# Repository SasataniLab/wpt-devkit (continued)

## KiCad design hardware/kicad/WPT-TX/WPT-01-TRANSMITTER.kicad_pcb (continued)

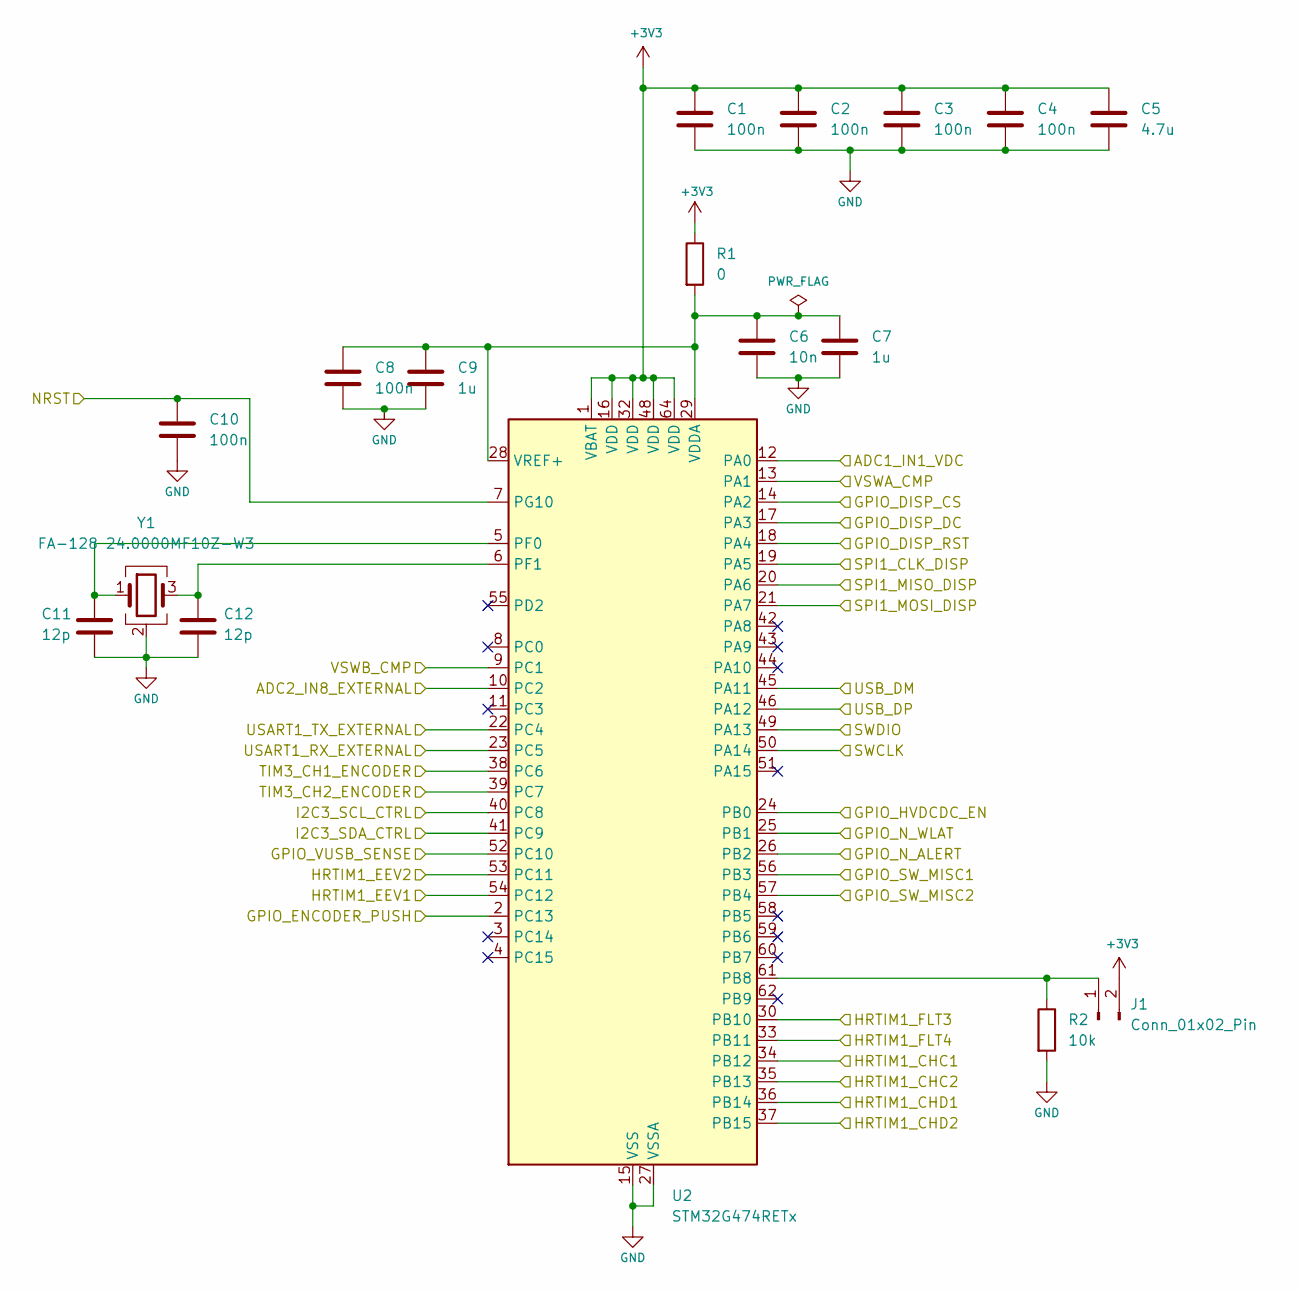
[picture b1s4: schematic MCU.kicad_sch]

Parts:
C1, C2, C3, C4, C8, C10: 100n; C_0402_1005Metric
C5: 4.7u; C_0402_1005Metric
C6: 10n; C_0402_1005Metric
C7, C9: 1u; C_0402_1005Metric
C11, C12: 12p; C_0402_1005Metric
J1: Conn_01x02_Pin; PinHeader_1x02_P2.54mm_Vertical
R1: 0; R_0402_1005Metric
R2: 10k; R_0402_1005Metric
U2: STM32G474RETx; LQFP-64_10x10mm_P0.5mm
Y1: FA-128 24.0000MF10Z-W3; Crystal_SMD_SeikoEpson_FA128-4Pin_2.0x1.6mm

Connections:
+3V3: C1.1, C2.1, C3.1, C4.1, C5.1, J1.2, R1.1, U2.1 (VBAT), U2.16 (VDD), U2.32 (VDD), U2.48 (VDD), U2.64 (VDD); also elsewhere on the board
/GPIO_VUSB_SENSE: U2.52 (PC10); also elsewhere on the board
/HRTIM1_CHC1: U2.34 (PB12); also elsewhere on the board
/HRTIM1_CHC2: U2.35 (PB13); also elsewhere on the board
/HRTIM1_CHD1: U2.36 (PB14); also elsewhere on the board
/HRTIM1_CHD2: U2.37 (PB15); also elsewhere on the board
/HRTIM1_EEV1: U2.54 (PC12); also elsewhere on the board
/HRTIM1_EEV2: U2.53 (PC11); also elsewhere on the board
/HRTIM1_FLT3: U2.30 (PB10); also elsewhere on the board
/HRTIM1_FLT4: U2.33 (PB11); also elsewhere on the board
/HV_EN_MCU: U2.24 (PB0); also elsewhere on the board
/HV_SW_STATE: U2.57 (PB4); also elsewhere on the board
/MCU/ADC2_IN8_EXTERNAL: U2.10 (PC2); also elsewhere on the board
/MCU/GPIO_DISP_CS: U2.14 (PA2); also elsewhere on the board
/MCU/GPIO_DISP_DC: U2.17 (PA3); also elsewhere on the board
/MCU/GPIO_DISP_RST: U2.18 (PA4); also elsewhere on the board
/MCU/GPIO_ENCODER_PUSH: U2.2 (PC13); also elsewhere on the board
/MCU/GPIO_SW_MISC1: U2.56 (PB3); also elsewhere on the board
/MCU/NRST: C10.1, U2.7 (PG10); also elsewhere on the board
/MCU/SPI1_CLK_DISP: U2.19 (PA5); also elsewhere on the board
/MCU/SPI1_MISO_DISP: U2.20 (PA6); also elsewhere on the board
/MCU/SPI1_MOSI_DISP: U2.21 (PA7); also elsewhere on the board
/MCU/SWCLK: U2.50 (PA14); also elsewhere on the board
/MCU/SWDIO: U2.49 (PA13); also elsewhere on the board
/MCU/TIM3_CH1_ENCODER: U2.38 (PC6); also elsewhere on the board
/MCU/TIM3_CH2_ENCODER: U2.39 (PC7); also elsewhere on the board
/MCU/USART1_RX_EXTERNAL: U2.23 (PC5); also elsewhere on the board
/MCU/USART1_TX_EXTERNAL: U2.22 (PC4); also elsewhere on the board
/USB_DM: U2.45 (PA11); also elsewhere on the board
/USB_DP: U2.46 (PA12); also elsewhere on the board
/VSWA_CMP: U2.13 (PA1); also elsewhere on the board
/VSWB_CMP: U2.9 (PC1); also elsewhere on the board
/WPT-01-TRANSMITTER-POWER/ADC_VDC: U2.12 (PA0); also elsewhere on the board
/WPT-01-TRANSMITTER-POWER/SCL: U2.40 (PC8); also elsewhere on the board
/WPT-01-TRANSMITTER-POWER/SDA: U2.41 (PC9); also elsewhere on the board
/WPT-01-TRANSMITTER-POWER/~ALERT: U2.26 (PB2); also elsewhere on the board
/WPT-01-TRANSMITTER-POWER/~WLAT: U2.25 (PB1); also elsewhere on the board
GND: C1.2, C2.2, C3.2, C4.2, C5.2, C6.2, C7.2, C8.2, C9.2, C10.2, C11.2, C12.2, R2.2, U2.15 (VSS), U2.27 (VSSA), U2.31 (VSS), U2.47 (VSS), U2.63 (VSS), Y1.2 (G), Y1.4 (G); also elsewhere on the board
unnamed: J1.1, R2.1, U2.61 (PB8)
unnamed: C11.1, U2.5 (PF0), Y1.1
unnamed: C12.1, U2.6 (PF1), Y1.3
unnamed: C6.1, C7.1, C8.1, C9.1, R1.2, U2.28 (VREF+), U2.29 (VDDA)

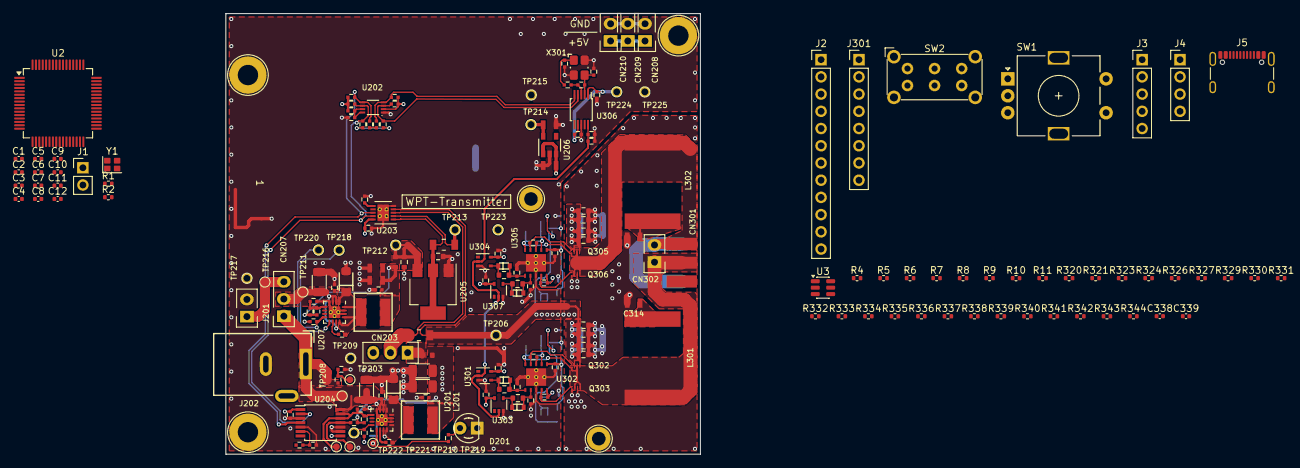
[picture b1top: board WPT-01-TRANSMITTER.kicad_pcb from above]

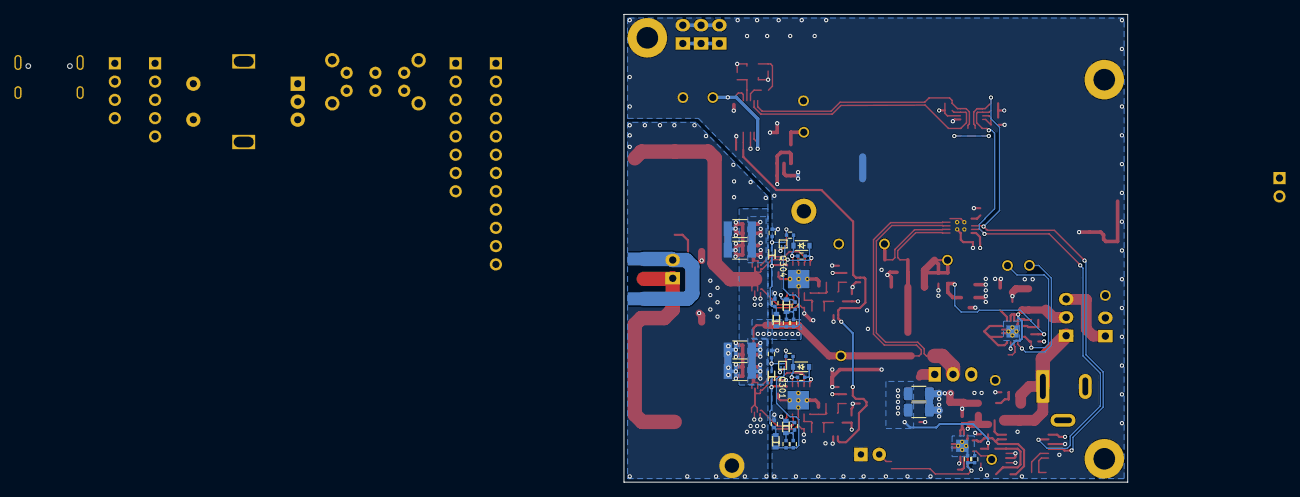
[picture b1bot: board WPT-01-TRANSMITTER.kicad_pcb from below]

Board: 4 copper layers, 70.0 x 65.0 mm, 230 parts (32 on the bottom side), 114 nets.

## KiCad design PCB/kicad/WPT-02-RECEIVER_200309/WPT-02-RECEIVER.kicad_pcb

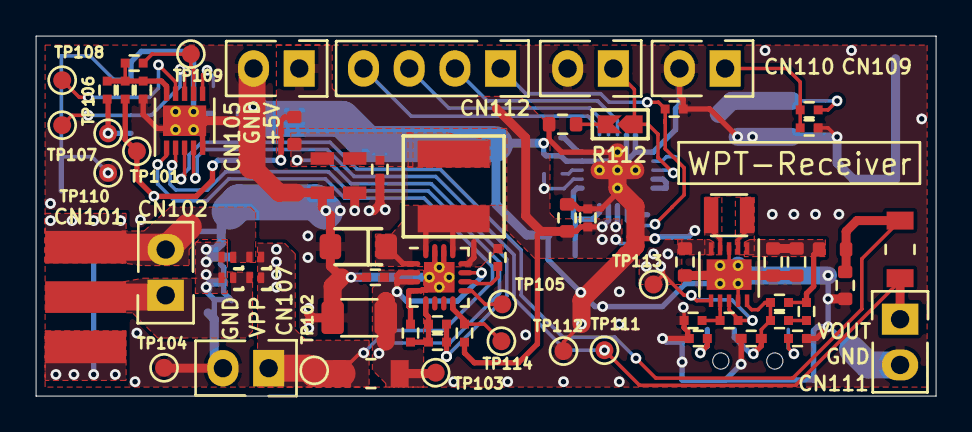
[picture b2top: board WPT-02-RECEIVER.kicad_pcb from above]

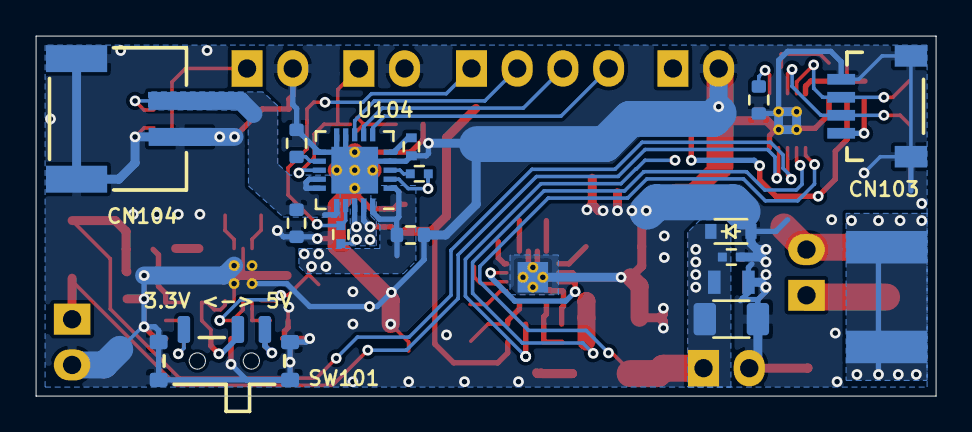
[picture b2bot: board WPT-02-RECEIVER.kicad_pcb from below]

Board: 4 copper layers, 50.0 x 20.0 mm, 84 parts (15 on the bottom side), 40 nets.

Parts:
C101: 0.022u/50(X7R); GRM15
C102, C107: 10u/50(X5R); GRM31
C103, C104, C116, C119: 0.1u/50(X7R); GRM15
C105: 1000p/50(C0G); GRM15
C106: 0.1u/100(X7R); GRM21
C108, C109: 22u/16(X5R); GRM21
C110: 10n/50(X7R); GRM15
C111: 10u/25(X5R); GRM18
C112, C122: 22u/10(X5R); GRM18
C113: 68p/50(C0G); GRM15
C117, C118, C120: 4.7u/16(X5R); GRM18
C123: OPEN; GRM18
CN101: CON-SMA-EDGE-S
CN102, CN105, CN107, CN109, CN110, CN111: ULO-PH409-1*2SF11; ULO-PH409-1x2SX1
CN103: SM04B-SRSS-TB(LF)(SN); SM04B-SRSS-TB
CN104: S2B-PH-SM4-TB(LF)(SN); S2B-PH-SM4-TB
CN112: ULO-PH409-1*4SF11; ULO-PH409-1x4SX1
D101, D102, D105, D106: PMEG6010AESBYL; SOD-993_Nexperia
D103: S210FA; SOD-123FA_OnSemi
D104: MM3Z39VT1G; SOD-323
FB101, FB102: BLM18PG330SN1D; BLM18
L101: NR5040T4R7N; NR5040
L102: DFE252012P-3R3M=P2; DFE252012C
R101: 82kF; R_0402
R102: 18kF; R_0402
R103, R107: 27mF(1/4W); R_1206
R104, R116: 10kF; R_0402
R105, R106, R108, R114, R119: OPEN; R_0402
R109: 750kF; R_0402
R110: 91kF; R_0402
R111: 820kF; R_0402
R112: SHORT_JUMPER; JP_SMD
R113, R115: 0; R_0402
R117: 0; R_0603
R118: NCP15XH103F03RC; NTC_0402
R120, R126: 100kF; R_0402
R121: 143kF; R_0402
R123: 100kF; R_0603
R124: 10kF; R_0603
SW101: CUS-12TB
TP101, TP102, TP103, TP104, TP105, TP106, TP107, TP108, TP109, TP110, TP111, TP112, TP113, TP114: TP1.0; TP_1mm
U101: TS30042-M000QFNR; QFN-16-1EP_3x3mm_Pitch0.5mm_Semtech
U102: MP2155GQ-Z; DFN-10-1EP_3x3mm_Pitch0.5mm_MPS
U103: PAC1720-1-AIA-TR; DFN-10-1EP_3x3mm_Pitch0.5mm_microchip_9Q
U104: MCP73871T-1CCI_ML; QFN-20-1EP_4x4mm_Pitch0.5mm_microchip_ML
VD101: CG0402MLC-3.3LG; CG0402

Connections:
+5V: C118.1, C119.1, CN105.1, FB101.2, R104.2, R114.2, R119.2, R120.2, TP101.1, U104.2, U104.18, U104.19
/CHG_EN: CN112.1, R119.1, R126.2, U104.17
/CHG_STAT1: CN112.2, U104.8
/CHG_STAT2: CN112.3, U104.7
/PWRGD_5V: R104.1, TP114.1, U101.8
/SCL: CN103.3, TP108.1, U103.9
/SDA: CN103.2, TP107.1, U103.8
/VEXT: CN103.1, R115.1, TP106.1
/VOUT: CN111.1, R107.1, TP111.1, U103.4
/~ALERT: R116.1, TP109.1, U103.7
/~CHG_PG: CN112.4, U104.6
GND: C102.2, C103.2, C104.2, C105.2, C106.2, C107.2, C108.2, C109.2, C111.2, C112.2, C116.2, C117.2, C118.2, C119.2, C120.2, C122.2, C123.2, CN103.4, CN103.FG, CN104.2, CN104.FG, CN105.2, CN107.2, CN109.2, CN110.2, CN111.2, D103.2, D104.2, D105.2, D106.2, R102.1, R106.1, R110.1, R113.1, R117.1, R118.1, R121.1, R123.1, R124.1, R126.1, SW101.FG, TP104.1, TP110.1, TP112.1, U101.4, U101.14, U101.15, U101.17, U102.3, U102.9, U102.11, U103.5, U103.11, U104.4, U104.9, U104.10, U104.11, U104.21, VD101.1
unnamed: C101.1, U101.10
unnamed: C101.2, D103.1, L101.1, U101.1, U101.12, U101.13, U101.16
unnamed: C102.1, C103.1, R103.1, TP103.1, U101.2, U101.3, U101.11, U103.2
unnamed: C104.1, C108.1, C109.1, C110.1, FB101.1, L101.2, R101.2
unnamed: C110.2, R101.1, R102.2, U101.5
unnamed: C112.1, C122.1, FB102.1, R109.2, R111.2, U102.1
unnamed: C113.1, R109.1
unnamed: C113.2, R111.1, SW101.2, U102.10, VD101.2
unnamed: C116.1, R114.1, R115.2, R116.2, U103.10
unnamed: C120.1, CN104.1, R105.2, U104.14, U104.15, U104.16
unnamed: C123.1, FB102.2, R107.2, U103.3
unnamed: CN101.1, CN102.1, D101.2, D105.1
unnamed: CN101.2, CN102.2, D102.2, D106.1
unnamed: CN109.1, R105.1, R106.2
unnamed: CN110.1, R112.2, U104.13
unnamed: L102.1, U102.4
unnamed: L102.2, U102.2
unnamed: R108.1, R113.2, U102.7
unnamed: R110.2, SW101.3
unnamed: R112.1, R124.2
unnamed: R117.2, U103.6
unnamed: R118.2, U104.5
unnamed: R120.1, U104.3
unnamed: R121.2, SW101.1
unnamed: R123.2, U104.12
unnamed: TP105.1, U101.9
VCC: C111.1, C117.1, R108.2, TP113.1, U102.5, U102.6, U102.8, U104.1, U104.20
VPP: C105.1, C106.1, C107.1, CN107.1, D101.1, D102.1, D104.1, R103.2, TP102.1, U103.1

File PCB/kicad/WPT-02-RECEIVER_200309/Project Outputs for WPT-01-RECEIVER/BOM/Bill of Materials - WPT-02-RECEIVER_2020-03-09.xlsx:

Source: | E:\Dropbox\dev\prj\commissioned\University of Tokyo\WPT\electric\kicad\WPT-02-R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
Date: | 09/03/2020 07:57:30
Tool: | Eeschema (5.1.5)-3
Generator: | E:\Dropbox\dev\prj\kicad-library/bom_csv_grouped_by_value_with_fp.py
Component Count: | 84
Mount | Comment | Description | Designator | Footprint | Manufacturer | Manufacturer Part Number | Qnty | Qty for 25Units | Retailer
Yes | 0.022u/50(X7R) | CAP CER 0.022UF 50V X7R 0402 | C101, | murata:GRM15 | Murata Electronics | GRM155R71H223KA12D | 1 | 25
Yes | 10u/50(X5R) | CAP CER 10UF 50V X5R 1206 | C102, C107, | murata:GRM31 | Samsung Electro-Mechanics | CL31A106KBHNNNE | 2 | 50
Yes | 0.1u/50(X7R) | CAP CER 0.1UF 50V X7R 0402 | C103, C104, C116, C119, | murata:GRM15 | Murata Electronics | GCM155R71H104KE02D | 4 | 100
Yes | 1000p/50(C0G) | CAP CER 1000PF 50V 5% NP0 0402 | C105, | murata:GRM15 | Murata Electronics | GRM1555C1H102JA01D | 1 | 25
Yes | 0.1u/100(X7R) | CAP CER 0.1UF 100V X7R 0805 | C106, | murata:GRM21 | Murata Electronics | GCM21BR72A104KA37L | 1 | 25
Yes | 22u/16(X5R) | CAP CER 22UF 16V X5R 0805 | C108, C109, | murata:GRM21 | Samsung Electro-Mechanics | CL21A226MOCLRNC | 2 | 50
Yes | 10n/50(X7R) | CAP CER 10000PF 50V X7R 0402 | C110, | murata:GRM15 | Yageo | CC0402KRX7R9BB103 | 1 | 25
Yes | 10u/25(X5R) | CAP CER 10UF 25V 20% X5R 0603 | C111, | murata:GRM18 | Murata Electronics | GRM188R61E106MA73D | 1 | 25
Yes | 22u/10(X5R) | CAP CER 22UF 10V X5R 0603 | C112, C122, | murata:GRM18 | Murata Electronics | GRM188R61A226ME15D | 2 | 50
Yes | 68p/50(C0G) | CAP CER 68PF 50V C0G/NP0 0402 | C113, | murata:GRM15 | Murata Electronics | GCM1555C1H680JA16D | 1 | 25
Yes | 4.7u/16(X5R) | CAP CER 4.7UF 16V X5R 0603 | C117, C118, C120, | murata:GRM18 | Murata Electronics | GRM188R61C475KAAJD | 3 | 75
No | OPEN |  | C123, | murata:GRM18 |  |  | 1 | 25
No | CON-SMA-EDGE-S | CONN SMA JACK STR EDGE MNT | CN101, | RF_Solutions:CON-SMA-EDGE-S | RF Solutions | CON-SMA-EDGE-S | 1 | 25
No | ULO-PH409-1*2SF11 | CON HEADER 2 PIN THROUGHTHOLE 6.1/2.5/3mm HEIGHT | CN102, CN105, CN107, CN109, CN110, CN111, | ulo:ULO-PH409-1x2SX1 | ULO Electronic | ULO-PH409-1x2SX1 | 6 | 150
Yes | SM04B-SRSS-TB(LF)(SN) | CONN HEADER SH 4POS SIDE 1MM TIN | CN103, | Connectors_JST:SM04B-SRSS-TB | JST | SM04B-SRSS-TB(LF)(SN) | 1 | 25
Yes | S2B-PH-SM4-TB(LF)(SN) | CONN HEADER PH SIDE 2POS 2MM SMD | CN104, | Connectors_JST:S2B-PH-SM4-TB | JST | S2B-PH-SM4-TB(LF)(SN) | 1 | 25
No | ULO-PH409-1*4SF11 | CON HEADER 4 PIN THROUGHTHOLE 6.1/2.5/3mm HEIGHT | CN112, | ulo:ULO-PH409-1x4SX1 | ULO Electric | ULO-PH409-1*4SF11 | 1 | 25
Yes | PMEG6010AESBYL | DIODE SCHOTTKY 60V 1A DSN1006-2 | D101, D102, D105, D106, | Diodes_SMD:SOD-993_Nexperia | Nexperia | PMEG6010AESBYL | 4 | 100
Yes | S210FA | DIODE SCHOTTKY 100V 2A SOD123FA | D103, | Diodes_SMD:SOD-123FA_OnSemi | ON Semiconductor | S210FA | 1 | 25
Yes | MM3Z39VT1G | DIODE ZENER 39V 300MW SOD323 | D104, | Diodes_SMD:SOD-323 | ON Semiconductor | MM3Z39VT1G | 1 | 25
Yes | BLM18PG330SN1D | FERRITE CHIP 33 OHM 3000MA 0603 | FB101, FB102, | murata:BLM18 | Murata Electronics | BLM18PG330SN1D | 2 | 50
Yes | NR5040T4R7N | FIXED IND 4.7UH 3.1A 37.7 MOHM | L101, | taiyo-yuden:NR5040 | Taiyo Yuden | NR5040T4R7N | 1 | 25
Yes | DFE252012P-3R3M=P2 | FIXED IND 3.3UH 2.3A 140 MOHM | L102, | murata:DFE252012C | Murata Electronics | DFE252012P | 1 | 25
Yes | 82kF | RES SMD 82K OHM 1% 1/16W 0402 | R101, | yageo:R_0402 | Yageo | RC0402FR-0782KL | 1 | 25
Yes | 18kF | RES SMD 18K OHM 5% 1/16W 0402 | R102, | yageo:R_0402 | Yageo | RC0402FR-0718KL | 1 | 25
Yes | 27mF(1/4W) | RES 0.027 OHM 1% 1/4W 1206 3216Metric | R103, R107, | yageo:R_1206 | Yageo | RL1206FR-070R027L | 2 | 50
Yes | 10kF | RES SMD 10K OHM 1% 1/16W 0402 | R104, R116, | yageo:R_0402 | Yageo | RC0402FR-0710KL | 2 | 50
No | OPEN |  | R105, R106, R108, R114, R119, | yageo:R_0402 |  |  | 5 | 125
Yes | 750kF | RES SMD 750K OHM 1% 1/16W 0402 | R109, | yageo:R_0402 | Yageo | RC0402FR-07750KL | 1 | 25
Yes | 91kF | RES SMD 91K OHM 1% 1/16W 0402 | R110, | yageo:R_0402 | Yageo | RC0402FR-0791KL | 1 | 25
Yes | 820kF | RES SMD 820K OHM 1% 1/16W 0402 | R111, | yageo:R_0402 | Yageo | RC0402FR-07820KL | 1 | 25
Yes | 0 | RES SMD 0.0OHM JUMPER 1/16W 0402 | R113, R115, | yageo:R_0402 | Yageo | RC0402FR-070RL | 2 | 50
Yes | 0 | RES SMD 0.0OHM JUMPER 1/10W 0603 | R112, R117, | yageo:R_0603 | Yageo | RC0603FR-070RL | 2 | 50
Yes | NCP15XH103F03RC | THERMISTOR 10K OHM NTC 0402 SMD | R118, | murata:NTC_0402 | Murata Electronics | NCP15XH103F03RC | 1 | 25
Yes | 100kF | RES SMD 100K OHM 1% 1/16W 0402 | R120, R126, | yageo:R_0402 | Yageo | RC0402FR-07100KL | 2 | 50
Yes | 143kF | RES SMD 143K OHM 1% 1/16W 0402 | R121, | yageo:R_0402 | Yageo | RC0402FR-07143KL | 1 | 25
Yes | 100kF | RES SMD 100K OHM 1% 1/10W 0603 | R123, | yageo:R_0603 | Yageo | RC0603FR-07100KL | 1 | 25
Yes | 10kF | RES SMD 10K OHM 1% 1/10W 0603 | R124, | yageo:R_0603 | Yageo | RC0603FR-0710KL | 1 | 25
Yes | CUS-12TB | SWITCH SLIDE SPDT 300MA 4V | SW101, | Nidec_Copal_Electronics:CUS-12TB | Nidec Copal Electronics | CUS-12TB | 1 | 25
No | TP1.0 | TEST POINT 1mm | TP101, TP102, TP103, TP104, TP105, TP106, TP107, TP108, TP109, TP110, TP111, TP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 | TestPoint:TP_1mm |  |  | 14 | 350
Yes | TS30042-M000QFNR | IC REG BUCK ADJ 2A SYNC 16-VQFN | U101, | Housings_DFN_QFN:QFN-16-1EP_3x3mm_Pitch0.5mm_Semtech | Semtech | TS30042-M000QFNR | 1 | 25
Yes | MP2155GQ-Z | IC REG BCK BST 3.3V/ADJ 10QFN | U102, | Housings_DFN_QFN:DFN-10-1EP_3x3mm_Pitch0.5mm_MPS | Monolithic Power Systems Inc. | MP2155GQ-Z | 1 | 25
Yes | PAC1720-1-AIA-TR | IC CURRENT SENSE MON DUAL 10VDFN | U103, | Housings_DFN_QFN:DFN-10-1EP_3x3mm_Pitch0.5mm_microchip_9Q | microchip | PAC1720-1-AIA-TR | 1 | 25
Yes | MCP73871T-1CCI_ML | USB/AC BATTERY CHARGER 4.1V 6H Timer 3.1V LBO | U104, | Housings_DFN_QFN:QFN-20-1EP_4x4mm_Pitch0.5mm_microchip_ML | microchip | MCP73871T-1CCI/ML | 1 | 25
Yes | CG0402MLC-3.3LG | VARISTOR 3.3V 0402 | VD101, | bourns:CG0402 | Bourns Inc. | CG0402MLC-3.3LG | 1 | 25

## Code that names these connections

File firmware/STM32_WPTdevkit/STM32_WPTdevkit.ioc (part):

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Mcu.Name=STM32G474R(B-C-E)Tx
Mcu.Package=LQFP64
Mcu.UserName=STM32G474RETx
PA0.GPIOParameters=GPIO_Label
PA0.GPIO_Label=ADC1_IN1_VDC
PA0.Mode=IN1-Single-Ended
PA0.Signal=ADC1_IN1
PA1.GPIOParameters=GPIO_Label
PA1.GPIO_Label=VSWA_CMP
PA1.Mode=INP
PA1.Signal=COMP1_INP
PA11.Mode=Device
PA11.Signal=USB_DM
PA12.Mode=Device
PA12.Signal=USB_DP
PA13.Mode=Serial_Wire
PA13.Signal=SYS_JTMS-SWDIO
PA14.Mode=Serial_Wire
PA14.Signal=SYS_JTCK-SWCLK
PA2.GPIOParameters=GPIO_Label
PA2.GPIO_Label=GPIO_DISP_CS
PA2.Signal=GPIO_Output
PA3.GPIOParameters=GPIO_Label
PA3.GPIO_Label=GPIO_DISP_DC
PA3.Signal=GPIO_Output
PA4.GPIOParameters=GPIO_Label
PA4.GPIO_Label=GPIO_DISP_RST
PA4.Signal=GPIO_Output
PA5.GPIOParameters=GPIO_Label
PA5.GPIO_Label=SPI1_CLK_DISP
PA5.Mode=Full_Duplex_Master
PA5.Signal=SPI1_SCK
PA6.GPIOParameters=GPIO_Label
PA6.GPIO_Label=SPI1_MISO_DISP
PA6.Mode=Full_Duplex_Master
PA6.Signal=SPI1_MISO
PA7.GPIOParameters=GPIO_Label
PA7.GPIO_Label=SPI1_MOSI_DISP
PA7.Mode=Full_Duplex_Master
PA7.Signal=SPI1_MOSI
PB0.GPIOParameters=GPIO_Label
PB0.GPIO_Label=GPIO_HVDCDC_EN
PB0.Signal=GPIO_Output
PB1.GPIOParameters=GPIO_Label
PB1.GPIO_Label=GPIO_N_WLAT
PB1.Signal=GPIO_Output
PB10.GPIOParameters=GPIO_Label
PB10.GPIO_Label=HRTIM1_FLT3_OCP
PB10.Mode=Fault_Enable3
PB10.Signal=HRTIM1_FLT3
PB11.GPIOParameters=GPIO_Label
PB11.GPIO_Label=HRTIM1_FLT4_EXT
PB11.Mode=Fault_Enable4
PB11.Signal=HRTIM1_FLT4
PB12.GPIOParameters=GPIO_Label
PB12.GPIO_Label=HRTIM1_CHC1_H_SIG1
PB12.Mode=Output_TC1TC2
PB12.Signal=HRTIM1_CHC1
PB13.GPIOParameters=GPIO_Label
PB13.GPIO_Label=HRTIM1_CHC2_L_SIG1
PB13.Mode=Output_TC1TC2
PB13.Signal=HRTIM1_CHC2
PB14.GPIOParameters=GPIO_Label
PB14.GPIO_Label=HRTIM1_CHD1_H_SIG2
PB14.Mode=Output_TD1TD2
PB14.Signal=HRTIM1_CHD1
PB15.GPIOParameters=GPIO_Label
PB15.GPIO_Label=HRTIM1_CHD2_L_SIG2
PB15.Mode=Output_TD1TD2
PB15.Signal=HRTIM1_CHD2
PB2.GPIOParameters=GPIO_Label
PB2.GPIO_Label=GPIO_N_ALERT
PB2.Signal=GPIO_Input
PB3.GPIOParameters=GPIO_Label
PB3.GPIO_Label=GPIO_SW_MISC1
PB3.Signal=GPIO_Input
PB4.GPIOParameters=GPIO_Label
PB4.GPIO_Label=GPIO_SW_MISC2
PB4.Signal=GPIO_Input
PC1.GPIOParameters=GPIO_Label
PC1.GPIO_Label=VSWB_CMP
PC1.Mode=INP
PC1.Signal=COMP3_INP
PC10.GPIOParameters=GPIO_Label
PC10.GPIO_Label=GPIO_VUSB_SENSE
PC10.Signal=GPIO_Input
PC11.GPIOParameters=GPIO_Label
PC11.GPIO_Label=HRTIM1_EEV2_ZVS_B
PC11.Mode=External_Evt_enable2
PC11.Signal=HRTIM1_EEV2
PC12.GPIOParameters=GPIO_Label
PC12.GPIO_Label=HRTIM1_EEV1_ZVS_A
PC12.Mode=External_Evt_enable1
PC12.Signal=HRTIM1_EEV1
PC13.GPIOParameters=GPIO_Label
PC13.GPIO_Label=GPIO_ENCODER_PUSH
PC13.Signal=GPIO_Input
PC2.GPIOParameters=GPIO_Label
PC2.GPIO_Label=ADC2_IN8_EXTERNAL
PC2.Mode=IN8-Single-Ended
PC2.Signal=ADC2_IN8
PC4.GPIOParameters=GPIO_Label
PC4.GPIO_Label=USART1_TX_EXTERNAL
PC4.Mode=Asynchronous
PC4.Signal=USART1_TX
PC5.GPIOParameters=GPIO_Label
PC5.GPIO_Label=USART1_RX_EXTERNAL
PC5.Mode=Asynchronous
PC5.Signal=USART1_RX
PC6.GPIOParameters=GPIO_Label
PC6.GPIO_Label=TIM3_CH1_ENCODER
PC6.Signal=S_TIM3_CH1
PC7.GPIOParameters=GPIO_Label
PC7.GPIO_Label=TIM3_CH2_ENCODER
PC7.Signal=S_TIM3_CH2
PC8.GPIOParameters=GPIO_Label
PC8.GPIO_Label=I2C3_SCL_CTRL
PC8.Mode=I2C
PC8.Signal=I2C3_SCL
PC9.GPIOParameters=GPIO_Label
PC9.GPIO_Label=I2C3_SDA_CTRL
PC9.Mode=I2C
PC9.Signal=I2C3_SDA
PF0-OSC_IN.Mode=HSE-External-Oscillator
PF0-OSC_IN.Signal=RCC_OSC_IN
PF1-OSC_OUT.Mode=HSE-External-Oscillator
PF1-OSC_OUT.Signal=RCC_OSC_OUT
RCC.HSE_VALUE=24000000
RCC.SYSCLKFreq_VALUE=170000000
RCC.SYSCLKSource=RCC_SYSCLKSOURCE_PLLCLK
board=custom

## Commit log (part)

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2022-04-05 Create wpt_toolkit_TX.ino
    init commit
2022-04-05 changed filename
2022-04-05 copied sleep
    https://www.hiramine.com/physicalcomputing/atmega328/sleepbuttonwakeup.html
2022-04-06 comment out sleep
2022-04-06 added pcb schmatic pdf
2022-04-06 hoge
2022-04-14 added pcb files
2023-10-30 add arduino file for mode switching
2024-07-09 Add initial firmware
2024-07-19 draft scpi interface and working
2024-07-19 add initial command reference
2024-07-19 Add power on/off commands
2024-07-19 organize dir
2024-07-20 update command reference
2024-07-20 updated fw commands
2024-07-22 Create LICENSE
2024-08-02 add gitignore
2024-08-02 make arduino firmware a installable package
2024-08-02 moved command reference
2024-08-02 add some docs
2024-08-02 add notes on dependencies
